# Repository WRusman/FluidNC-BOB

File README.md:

# FluidNC-BOB
Break-Out Board for FluidNC made in Kicad 7

Devkit V1 model used : https://www.snapeda.com/parts/ESP32-DEVKIT-V1/Do%20it/view-part/?

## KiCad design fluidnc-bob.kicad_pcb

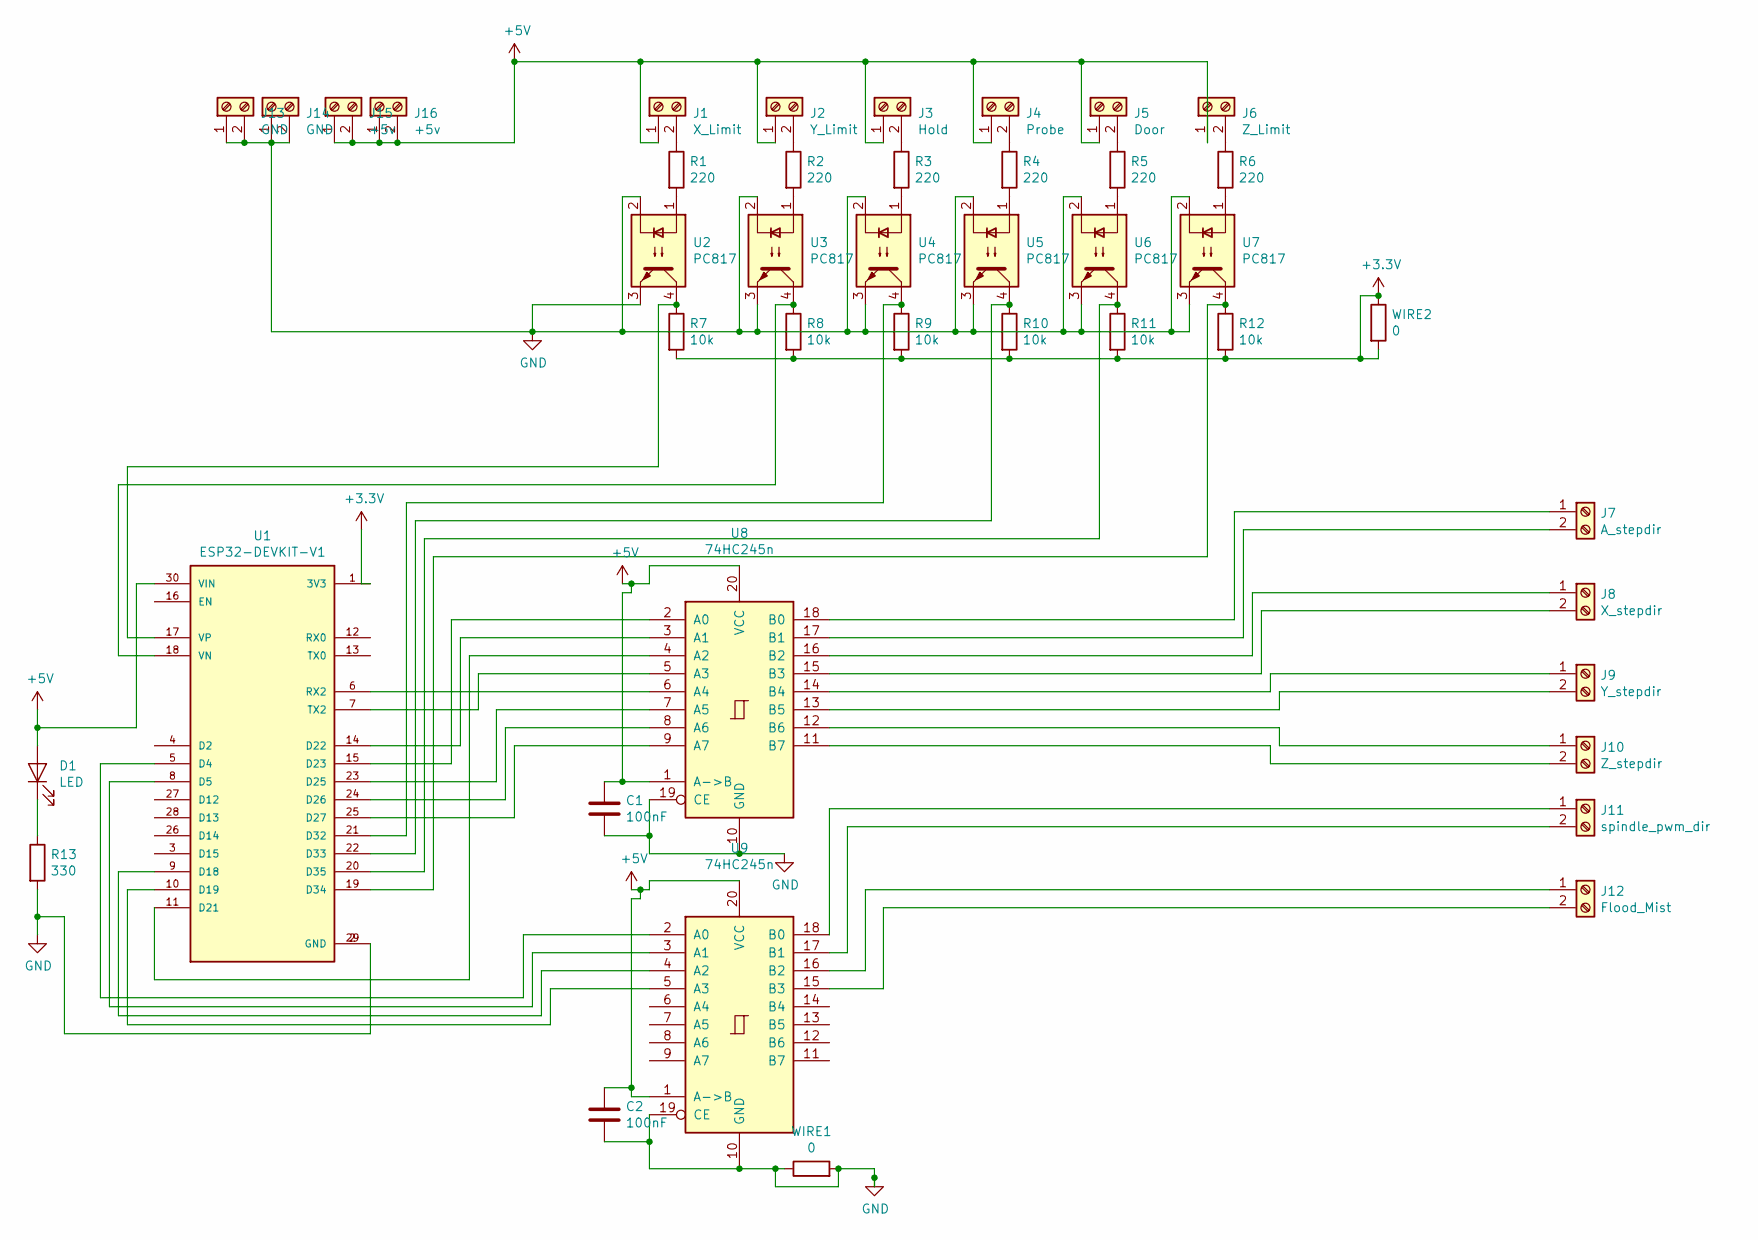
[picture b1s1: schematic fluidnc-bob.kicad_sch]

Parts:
C1, C2: 100nF; C_Axial_L3.8mm_D2.6mm_P7.50mm_Horizontal
D1: LED; LED_D5.0mm
J1: X_Limit; TerminalBlock_MetzConnect_Type073_RT02602HBLU_1x02_P5.08mm_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
J2: Y_Limit; TerminalBlock_MetzConnect_Type073_RT02602HBLU_1x02_P5.08mm_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
J3: Hold; TerminalBlock_MetzConnect_Type073_RT02602HBLU_1x02_P5.08mm_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
J4: Probe; TerminalBlock_MetzConnect_Type073_RT02602HBLU_1x02_P5.08mm_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
J5: Door; TerminalBlock_MetzConnect_Type073_RT02602HBLU_1x02_P5.08mm_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
J6: Z_Limit; TerminalBlock_MetzConnect_Type073_RT02602HBLU_1x02_P5.08mm_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
J7: A_stepdir; TerminalBlock_MetzConnect_Type073_RT02602HBLU_1x02_P5.08mm_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
J8: X_stepdir; TerminalBlock_MetzConnect_Type073_RT02602HBLU_1x02_P5.08mm_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
J9: Y_stepdir; TerminalBlock_MetzConnect_Type073_RT02602HBLU_1x02_P5.08mm_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
J10: Z_stepdir; TerminalBlock_MetzConnect_Type073_RT02602HBLU_1x02_P5.08mm_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
J11: spindle_pwm_dir; TerminalBlock_MetzConnect_Type073_RT02602HBLU_1x02_P5.08mm_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
J12: Flood_Mist; TerminalBlock_MetzConnect_Type073_RT02602HBLU_1x02_P5.08mm_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
J13, J14: GND; TerminalBlock_MetzConnect_Type073_RT02602HBLU_1x02_P5.08mm_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
J15, J16: +5v; TerminalBlock_MetzConnect_Type073_RT02602HBLU_1x02_P5.08mm_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
R1, R2, R3, R4, R5, R6: 220; R_Axial_DIN0204_L3.6mm_D1.6mm_P7.62mm_Horizontal
R7, R8, R9, R10, R11, R12: 10k; R_Axial_DIN0204_L3.6mm_D1.6mm_P7.62mm_Horizontal
R13: 330; R_Axial_DIN0204_L3.6mm_D1.6mm_P7.62mm_Horizontal
U1: ESP32-DEVKIT-V1; MODULE_ESP32_DEVKIT_V1; PARTREV N/A
U2, U3, U4, U5, U6, U7: PC817; DIP-4_W7.62mm
U8, U9: 74HC245n; DIP-20_W7.62mm_Socket_LongPads
WIRE1, WIRE2: 0; R_Axial_DIN0207_L6.3mm_D2.5mm_P7.62mm_Horizontal

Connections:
+3V3: R7.2, R8.2, R9.2, R10.2, R11.2, R12.2, U1.1 (3V3), WIRE2.1, WIRE2.2
+5V: C1.1, C2.1, D1.2 (A), J1.1, J2.1, J3.1, J4.1, J5.1, J6.1, J15.1, J15.2, J16.1, J16.2, U1.30 (VIN), U8.1 (A->B), U8.20 (VCC), U9.1 (A->B), U9.20 (VCC)
GND: C1.2, C2.2, J13.1, J13.2, J14.1, J14.2, R13.2, U1.2 (GND), U1.29 (GND), U2.2, U2.3, U3.2, U3.3, U4.2, U4.3, U5.2, U5.3, U6.2, U6.3, U7.2, U7.3, U8.10 (GND), U8.19 (CE), U9.10 (GND), U9.19 (CE), WIRE1.1, WIRE1.2
unnamed: D1.1 (K), R13.1
unnamed: J1.2, R1.1
unnamed: J2.2, R2.1
unnamed: J3.2, R3.1
unnamed: J4.2, R4.1
unnamed: J5.2, R5.1
unnamed: J6.2, R6.1
unnamed: J7.1, U8.18 (B0)
unnamed: J7.2, U8.17 (B1)
unnamed: J8.1, U8.16 (B2)
unnamed: J8.2, U8.15 (B3)
unnamed: J9.1, U8.14 (B4)
unnamed: J9.2, U8.13 (B5)
unnamed: J10.1, U8.12 (B6)
unnamed: J10.2, U8.11 (B7)
unnamed: J11.1, U9.18 (B0)
unnamed: J11.2, U9.17 (B1)
unnamed: J12.1, U9.16 (B2)
unnamed: J12.2, U9.15 (B3)
unnamed: R1.2, U2.1
unnamed: R2.2, U3.1
unnamed: R3.2, U4.1
unnamed: R4.2, U5.1
unnamed: R5.2, U6.1
unnamed: R6.2, U7.1
unnamed: R7.1, U1.17 (VP), U2.4
unnamed: R8.1, U1.18 (VN), U3.4
unnamed: R9.1, U1.21 (D32), U4.4
unnamed: R10.1, U1.22 (D33), U5.4
unnamed: R11.1, U1.20 (D35), U6.4
unnamed: R12.1, U1.19 (D34), U7.4
unnamed: U1.5 (D4), U9.2 (A0)
unnamed: U1.6 (RX2), U8.6 (A4)
unnamed: U1.7 (TX2), U8.5 (A3)
unnamed: U1.8 (D5), U9.3 (A1)
unnamed: U1.9 (D18), U9.4 (A2)
unnamed: U1.10 (D19), U9.5 (A3)
unnamed: U1.11 (D21), U8.4 (A2)
unnamed: U1.14 (D22), U8.3 (A1)
unnamed: U1.15 (D23), U8.2 (A0)
unnamed: U1.23 (D25), U8.7 (A5)
unnamed: U1.24 (D26), U8.8 (A6)
unnamed: U1.25 (D27), U8.9 (A7)

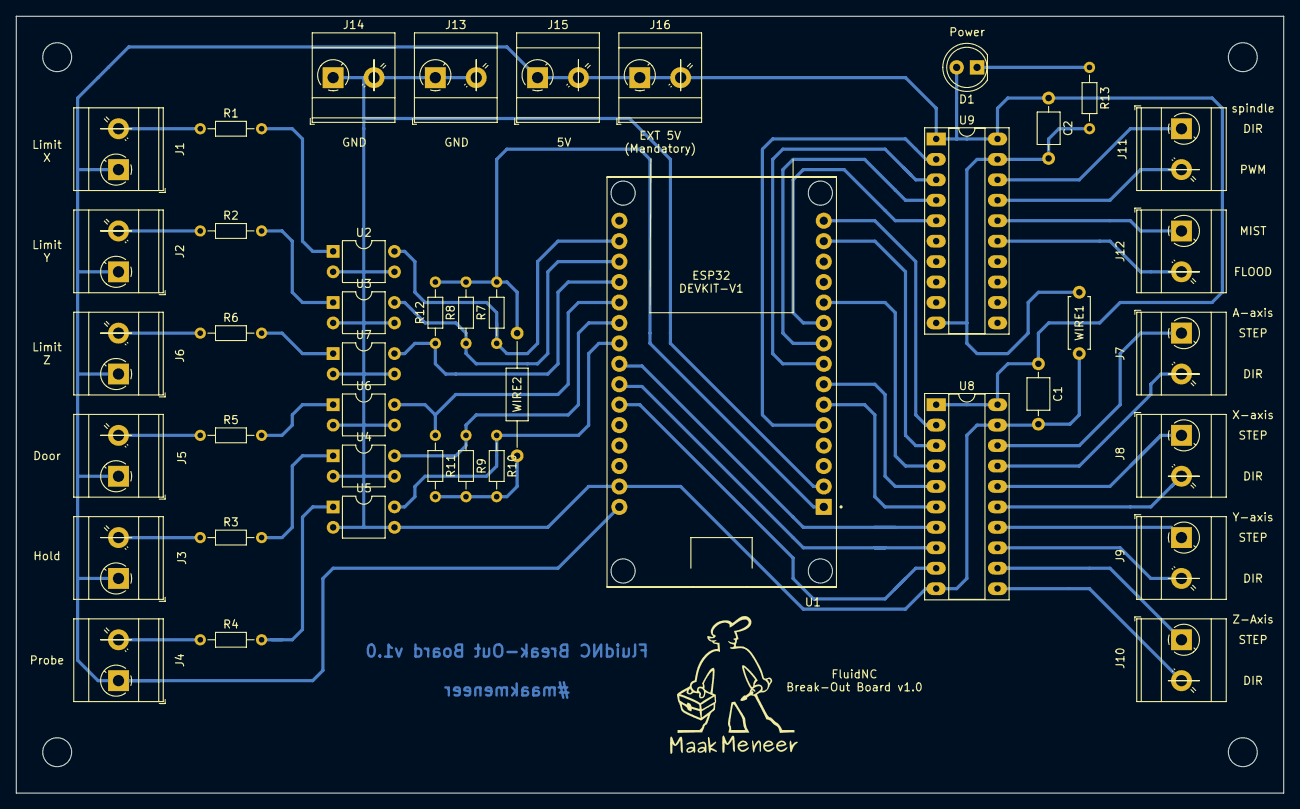
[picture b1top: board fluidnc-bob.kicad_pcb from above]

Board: 2 copper layers, 157.5 x 96.5 mm, 43 parts (0 on the bottom side), 46 nets.

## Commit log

2023-03-12 Create LICENSE
2023-03-12 Create ESP-DEVKIT-V1
